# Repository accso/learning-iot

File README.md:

# Learning IoT

Goody for Building IoT in Munich 25. - 27. April 2023.

## Images PCB

## Pin List

|  GPIO  |  Pin  |  Function    |
|--------|-------|--------------|
| GPIO0  |  D3   | Button / SW1 |
| GPIO2  |  D4   | LED Green    |
| GPIO15 |  D8   | LED Blue     |
| GPIO16 |  D0   | LED Red      |

## Bill of Materials (BOM)

All components can be ordered at http://reichelt.de

|      |   |     Order Number        |                      Description                         |
|------|---|-------------------------|----------------------------------------------------------|
| D1   | 1 | LED LL 5-8000RGBRGB-LED | 5 mm, bedrahtet, 4-Pin, rt/gn/bl, 8000 mcd, 25°          |
| SW1  | 1 | TASTER 3301             | Kurzhubtaster 6x6mm, Höhe: 4,3mm, 12V, vertikal          |
| U1   | 2 | MPE 087-1-008           | Stiftleisten 2,54 mm, 1X08, gerade                       |
| R4   | 1 | 1/4W 10K                | Widerstand, Kohleschicht, 10 kOhm, 0207, 250 mW, 5       |
| R1-3 | 3 | 1/4W 300                | Widerstand, Kohleschicht, 300 Ohm, 0207, 250 mW, 5%      |
|      | 1 | ESD BEUTEL-S 127        | ESD PE-Abschirmbeutel, wiederverschließbar, 76 x 127 mm  |

## Schematic

## Assembly

1) Bend the wires of the resistors by 90° <br>
2) Put the resistors through the holes (R4 is 10k while R1-3 is 330 Ohms)  <br>
3) Bend the wires by 30° and cut the pins, so 1mm wire is still visible from the bottom <br>  
4) Put the tactile button through the holes as described in following picture <br>
5) Put the LEDs through the holes with the flatted side pointed in direction of the push button
6) Bend the outer wires by 30° and cut all wires, so 1mm wire is still visible from the bottom <br>
7) Solder all components <br>
8) Solder the pin headers (male) downwards <br>
9) Solder the pin headers (female) on top of D1 mini, so the shield can be put on top. <br><br>

## Flashing firmware

See the latest release at the release page of Github!

**Install Firmware:**
```
pip3 install esptool
python3 -m esptool --port /dev/tty.usbserial-1440 --baud 115200 erase_flash 
python3 -m esptool --port /dev/tty.SLAB_USBtoUART --baud 115200 write_flash 0x0 firmware-v1.0-esp8266_learning-iot.bin
```

**WiFi-AP:**
SSID: Accso Learning IoT
Key: Accso Learning IoT

**URL**
http://192.168.4.1
http://accso-learning-iot.local

**Config-Area:**
User: admin
Password: admin

## SW API

### Initialize Board

To initialize the Learning IoT Board requires as parameter the pointer to the web server handling REST-API calls.

```
LIoTBoard.begin(&webServer);
```

### Setting LEDs

```
void LIoTBoard.setLed(String color);

color: Color as string. Can be:
 - "black"
 - "red"
 - "green"
 - "yellow"
 - "blue"
 - "purple"
 - "cyan"
 - "white"
```

```
void LIoTBoard.setLed(bool bRed, bool bGreen, bool bBlue);

bRed: LED red true = on, false = off

bGreen: LED green true = on, false = off

bBlue: LED blue true = on, false = off
```

### Read button
```
bool LIoTBoard.getButtonPressed(void);

returns: true if button pressed and false if button is released
```

## Getting started

### Driving LED without board support

[basic.ino](firmware/examples/basic/basic.ino)
```
#define LED_RED    16 // D0
#define LED_GREEN   2 // D4
#define LED_BLUE   15 // D8
#define BUTTON      0 // D3

void setup(void)
{
    pinMode(LED_RED,OUTPUT);
    pinMode(LED_GREEN,OUTPUT);
    pinMode(LED_BLUE,OUTPUT);
    pinMode(BUTTON,INPUT);
}

void loop(void)
{
    // blink red LED
    digitalWrite(LED_RED,HIGH);
    delay(500);
    digitalWrite(LED_RED,LOW);
    delay(500);

    // blink green LED
    digitalWrite(LED_GREEN,HIGH);
    delay(500);
    digitalWrite(LED_GREEN,LOW);
    delay(500);

    // blink blue LED
    digitalWrite(LED_BLUE,HIGH);
    delay(500);
    digitalWrite(LED_BLUE,LOW);
    delay(500);

    // wait for button pressed (blocking)
    while(digitalRead(BUTTON))
    {
        delay(1);
    }
}
```

### Driving LED with board support

[board-support.ino](firmware/examples/board-support/board-support.ino)
```
# requires to add liotboard.h and liotboard.cpp to the project
#include "liotboard.h"

void setup(void)
{
    LIoTBoard.begin();

    LIoTBoard.setLed("red");
}

void loop(void)
{
    LIoTBoard.update();
    if (LIoTBoard.getButtonPressed())
    {
        LIoTBoard.setLed("green");
    } else
    {
        LIoTBoard.setLed("red");
    }
}
```

### REST API Example

POST data with JSON content /api/status:
- "red": LED Red, allowed values: "true" or "false"
- "green": LED Green, allowed values: "true" or "false"
- "blue": LED Blue, allowed values: "true" or "false"
- "button": Button change overwrite, allowed values: "true" or "false"

GET data as JSON format /api/status:
- "red": LED Red, allowed values: "true" or "false"
- "green": LED Green, allowed values: "true" or "false"
- "blue": LED Blue, allowed values: "true" or "false"
- "button": Button status, allowed values: "true" or "false"

[restapi.ino](firmware/examples/restapi/restapi.ino)
```
#include <ESP8266WiFi.h>
#include <WiFiClient.h>
#include <ESP8266WebServer.h>
#include <ESP8266mDNS.h>

# requires to add liotboard.h and liotboard.cpp to the project
#include "liotboard.h"

#ifndef STASSID
#define STASSID "your-ssid"
#define STAPSK "your-password"
#endif

const char* ssid = STASSID;
const char* password = STAPSK;

ESP8266WebServer server(80);

void handleRoot() {
  server.send(200, "text/plain", "hello from esp8266!\r\n");
}

void setup(void) {
  Serial.begin(115200);
  WiFi.mode(WIFI_STA);
  WiFi.begin(ssid, password);
  Serial.println("");

  // Wait for connection
  while (WiFi.status() != WL_CONNECTED) {
    delay(500);
    Serial.print(".");
  }
  Serial.println("");
  Serial.print("Connected to ");
  Serial.println(ssid);
  Serial.print("IP address: ");
  Serial.println(WiFi.localIP());

  if (MDNS.begin("esp8266")) { Serial.println("MDNS responder started"); }

  LIoTBoard.begin(&server);
  server.on("/", handleRoot);

  server.begin();
  Serial.println("HTTP server started");
}

void loop(void) {
  server.handleClient();
  MDNS.update();
}
```

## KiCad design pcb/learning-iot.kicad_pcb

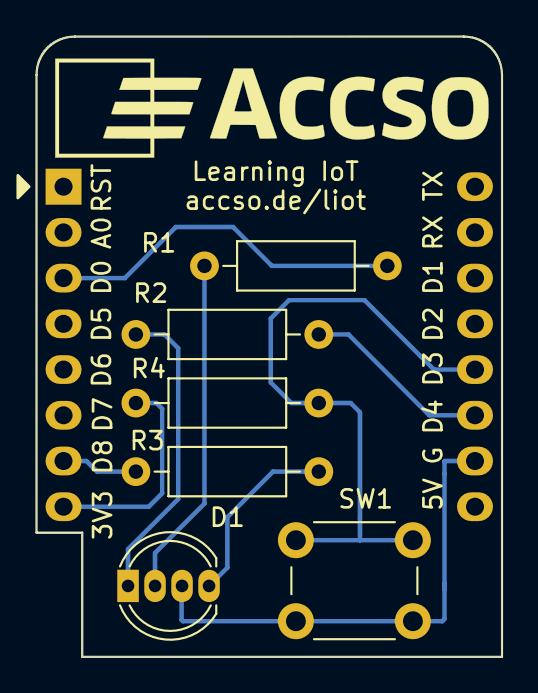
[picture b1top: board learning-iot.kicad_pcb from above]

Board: 2 copper layers, 25.8 x 34.5 mm, 7 parts (0 on the bottom side), 9 nets.

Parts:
D1: LED_GRCB; LEDLL5-8000RGB
R1, R2, R3, R4: R; R_Axial_DIN0207_L6.3mm_D2.5mm_P10.16mm_Horizontal
SW1: SW_Push; SW_PUSH_6mm_H4.3mm
U1: WeMos_D1_mini; WEMOS_D1_mini_light

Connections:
+3V3: R4.1, U1.8
GND: D1.3, SW1.2, U1.10
unnamed: D1.1, R2.1
unnamed: D1.2, R1.1
unnamed: D1.4, R3.1
unnamed: R1.2, U1.3
unnamed: R2.2, U1.11
unnamed: R3.2, U1.7
unnamed: R4.2, SW1.1, U1.12

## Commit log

2023-04-25 adding missing JSON library
2023-04-25 fixing missing ;
2023-04-25 updating DNS / Wifi AP Names
2023-04-25 Updating HTML content
2023-04-25 fixing API
2023-04-25 fixing statemachine
2023-04-25 updating example
2023-04-26 Readme updated with deployment information
